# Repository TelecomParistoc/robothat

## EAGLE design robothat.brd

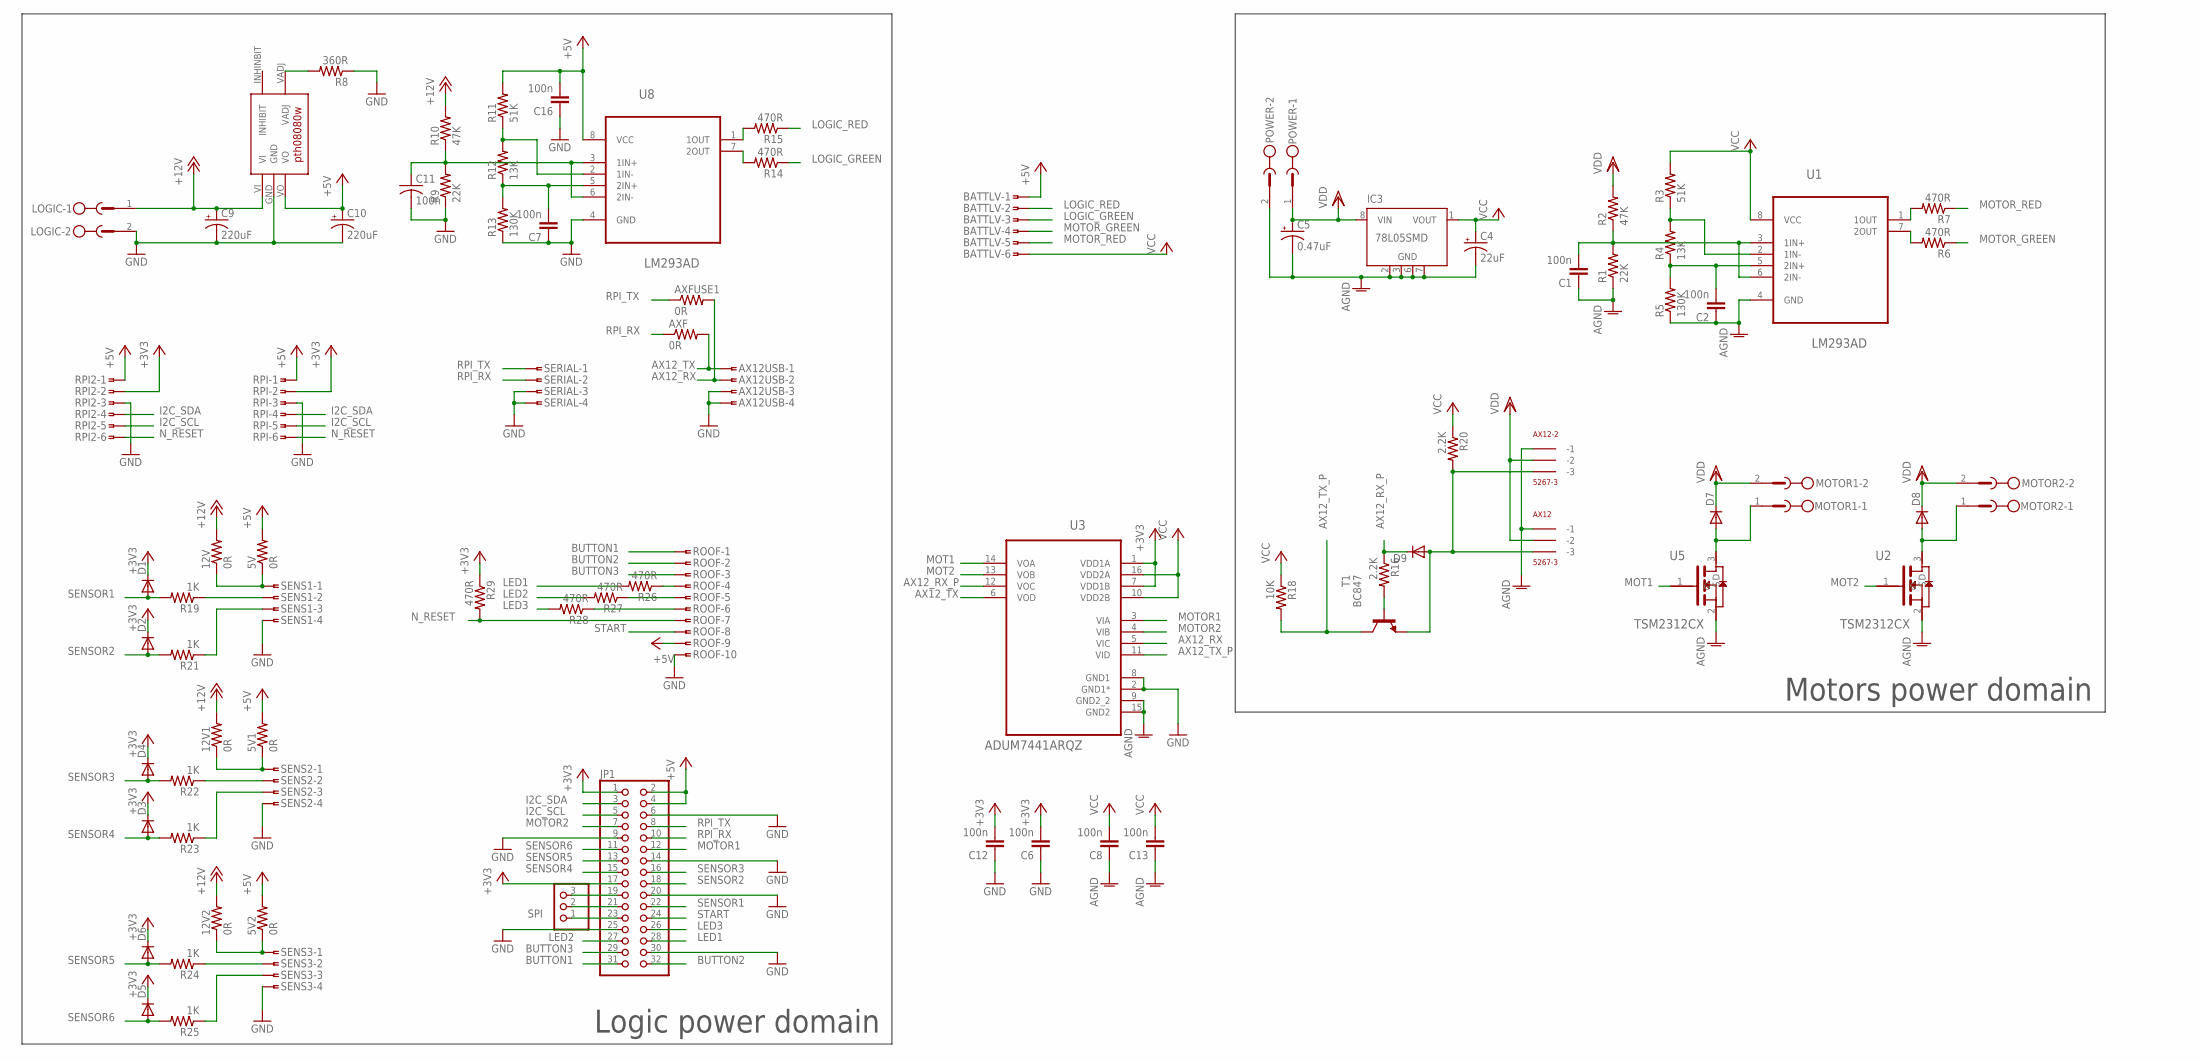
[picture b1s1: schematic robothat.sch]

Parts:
5V, 5V1, 5V2, 12V, 12V1, 12V2: 0R; R0805
AX12, AX12-2: 5267-3
AX12USB: SMDTOP-4; SMDTOP4
AXF: 0R; R0805
AXFUSE1: 0R; R0805
BATTLV: SMDTOP-6; SMDTOP6
C1, C2, C6, C7, C8, C11, C12, C13, C16: 100n; C0805
C4: 22uF; E2-5
C5: 0.47uF; E2-5
C9: 220uF; E3,5-8
C10: 220uF; E2,5-7
D1, D2, D3, D4, D5, D6, D9: DIODE-SOD523; SOD523
D7, D8: DIODE-SOD323-R; SOD323-R
IC3: 78L05SMD; SO08
JP1: PINHD-2X16; 2X16
LOGIC: MSTBV2
MOTOR1, MOTOR2: MSTBV2
POWER: MSTBV2
R1, R9: 22K; R0805
R2, R10: 47K; R0805
R3, R11: 51K; R0805
R4, R12: 13K; R0805
R5, R13: 130K; R0805
R6, R7, R14, R15, R26, R27, R28, R29: 470R; R0805
R8: 360R; R0805
R16, R20: 2.2K; R0805
R18: 10K; R0805
R19, R21, R22, R23, R24, R25: 1K; R0805
ROOF: SMDTOP-10; SMDTOP10
RPI, RPI2: SMDTOP-6; SMDTOP6
SENS1, SENS2, SENS3: SMDTOP-4; SMDTOP4
SERIAL: SMDTOP-4; SMDTOP4
SPI: PINHD-1X3; 1X03
T1: BC847; SOT23
U1, U8: LM293AD; SOIC127P600X175-8N
U2, U5: TSM2312CX; SOT95P280X130-3N
U3: ADUM7441ARQZ; SOP64P600X175-16N
U$2: REGUL_PTH

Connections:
+3V3: C6.2, C12.2, D1.C, D2.C, D3.C, D4.C, D5.C, D6.C, JP1.1, JP1.17, R29.1, RPI.2, RPI2.2, U3.1 (VDD1A), U3.7 (VDD1B)
+5V: 5V.2, 5V1.2, 5V2.2, BATTLV.1, C10.+, C16.2, JP1.2, JP1.4, R11.2, ROOF.9, RPI.1, RPI2.1, U8.8 (VCC), U$2.VO
+12V: 12V.2, 12V1.2, 12V2.2, C9.+, LOGIC.1, R10.2, U$2.VI
AGND: AX12.P$1 (-1), AX12-2.P$1 (-1), C1.1, C2.1, C4.-, C5.-, C8.1, C13.1, IC3.2 (GND), IC3.3 (GND), IC3.6 (GND), IC3.7 (GND), POWER.2, R1.1, R5.1, U1.4 (GND), U2.2 (S), U3.9 (GND2_2), U3.15 (GND2), U5.2 (S)
AX12_RX: AX12USB.2, AXFUSE1.2, U3.5 (VIC)
AX12_RX_P: D9.C, R16.1, U3.12 (VOC)
AX12_TX: AX12USB.1, AXF.2, U3.6 (VOD)
AX12_TX_P: R18.2, T1.3 (C), U3.11 (VID)
BUTTON1: JP1.31, ROOF.1
BUTTON2: JP1.32, ROOF.2
BUTTON3: JP1.29, ROOF.3
GND: AX12USB.3, AX12USB.4, C6.1, C7.1, C9.-, C10.-, C11.2, C12.1, C16.1, JP1.6, JP1.9, JP1.14, JP1.20, JP1.25, JP1.30, LOGIC.2, R8.1, R9.1, R13.1, ROOF.10, RPI.3, RPI2.3, SENS1.4, SENS2.4, SENS3.4, SERIAL.3, SERIAL.4, U3.2 (GND1*), U3.8 (GND1), U8.4 (GND), U$2.GND
I2C_SCL: JP1.5, RPI.5, RPI2.5
I2C_SDA: JP1.3, RPI.4, RPI2.4
LED1: JP1.28, R26.2
LED2: JP1.27, R27.2
LED3: JP1.26, R28.2
LOGIC_GREEN: BATTLV.3, R14.1
LOGIC_RED: BATTLV.2, R15.1
MOT1: U3.14 (VOA), U5.1 (G)
MOT2: U2.1 (G), U3.13 (VOB)
MOTOR1: JP1.12, U3.3 (VIA)
MOTOR2: JP1.7, U3.4 (VIB)
MOTOR_GREEN: BATTLV.4, R6.1
MOTOR_RED: BATTLV.5, R7.1
unnamed: R7.2, U1.1 (1OUT)
unnamed: D7.A, MOTOR1.1, U5.3 (D)
unnamed: R6.2, U1.7 (2OUT)
unnamed: D8.A, MOTOR2.1, U2.3 (D)
unnamed: C1.2, R1.2, R2.1, U1.3 (1IN+), U1.6 (2IN-)
unnamed: R3.1, R4.2, U1.2 (1IN-)
unnamed: C2.2, R4.1, R5.2, U1.5 (2IN+)
unnamed: 5V.1, 12V.1, SENS1.1
unnamed: 5V1.1, 12V1.1, SENS2.1
unnamed: R22.1, SENS2.2
unnamed: R19.1, SENS1.2
unnamed: R8.2, U$2.VADJ
unnamed: R15.2, U8.1 (1OUT)
unnamed: R14.2, U8.7 (2OUT)
unnamed: R21.1, SENS1.3
unnamed: C11.1, R9.2, R10.1, U8.3 (1IN+), U8.6 (2IN-)
unnamed: R11.1, R12.2, U8.2 (1IN-)
unnamed: C7.2, R12.1, R13.2, U8.5 (2IN+)
unnamed: R23.1, SENS2.3
unnamed: R16.2, T1.1 (B)
unnamed: AX12.P$3 (-3), AX12-2.P$3 (-3), D9.A, R20.2, T1.2 (E)
unnamed: 5V2.1, 12V2.1, SENS3.1
unnamed: R24.1, SENS3.2
unnamed: R25.1, SENS3.3
unnamed: R27.1, ROOF.5
unnamed: R26.1, ROOF.4
unnamed: R28.1, ROOF.6
unnamed: JP1.19, SPI.3
unnamed: JP1.21, SPI.2
unnamed: JP1.23, SPI.1
N_RESET: R29.2, ROOF.7, RPI.6, RPI2.6
RPI_RX: AXF.1, JP1.10, SERIAL.2
RPI_TX: AXFUSE1.1, JP1.8, SERIAL.1
SENSOR1: D1.A, JP1.22, R19.2
SENSOR2: D2.A, JP1.18, R21.2
SENSOR3: D4.A, JP1.16, R22.2
SENSOR4: D3.A, JP1.15, R23.2
SENSOR5: D6.A, JP1.13, R24.2
SENSOR6: D5.A, JP1.11, R25.2
START: JP1.24, ROOF.8
VCC: BATTLV.6, C4.+, C8.2, C13.2, IC3.1 (VOUT), R3.2, R18.1, R20.1, U1.8 (VCC), U3.10 (VDD2B), U3.16 (VDD2A)
VDD: AX12.P$2 (-2), AX12-2.P$2 (-2), C5.+, D7.C, D8.C, IC3.8 (VIN), MOTOR1.2, MOTOR2.2, POWER.1, R2.2

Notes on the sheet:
Logic power domain
Motors power domain

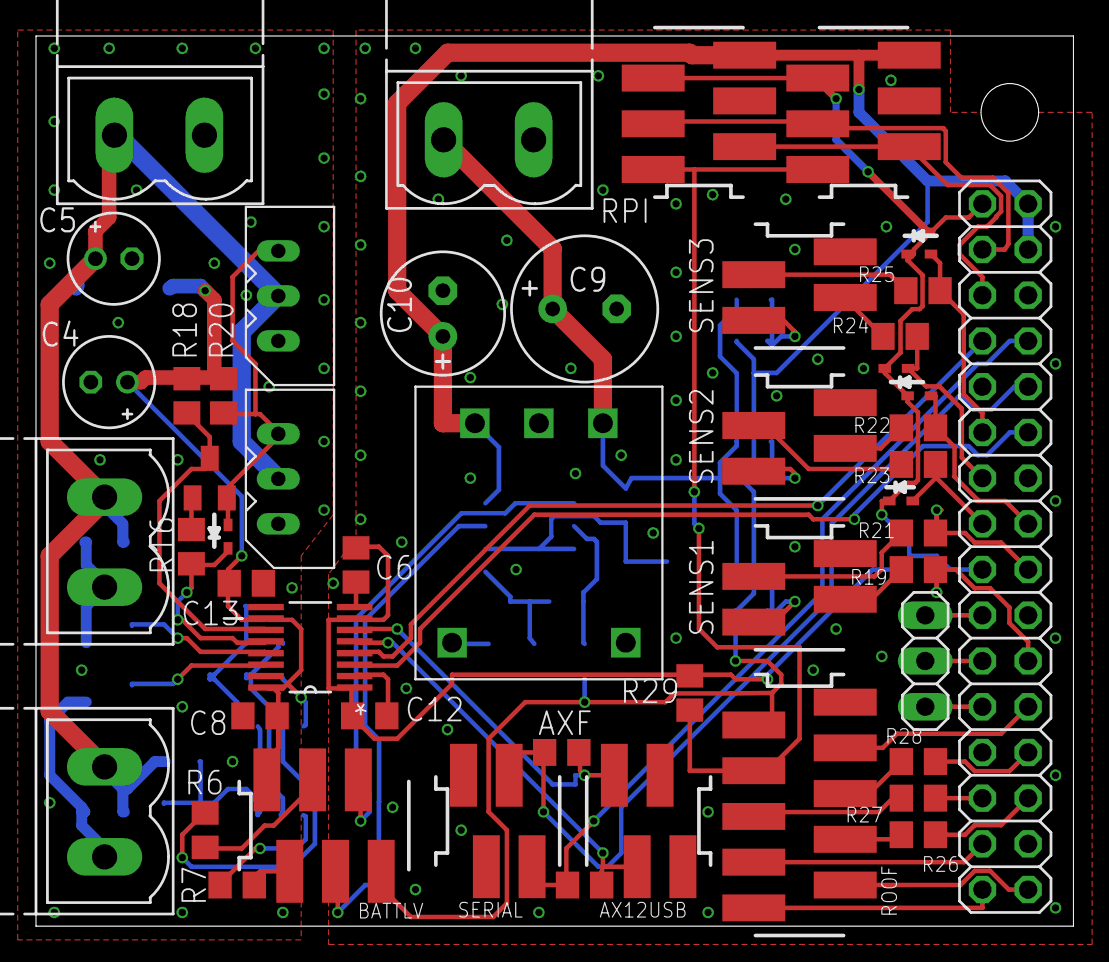
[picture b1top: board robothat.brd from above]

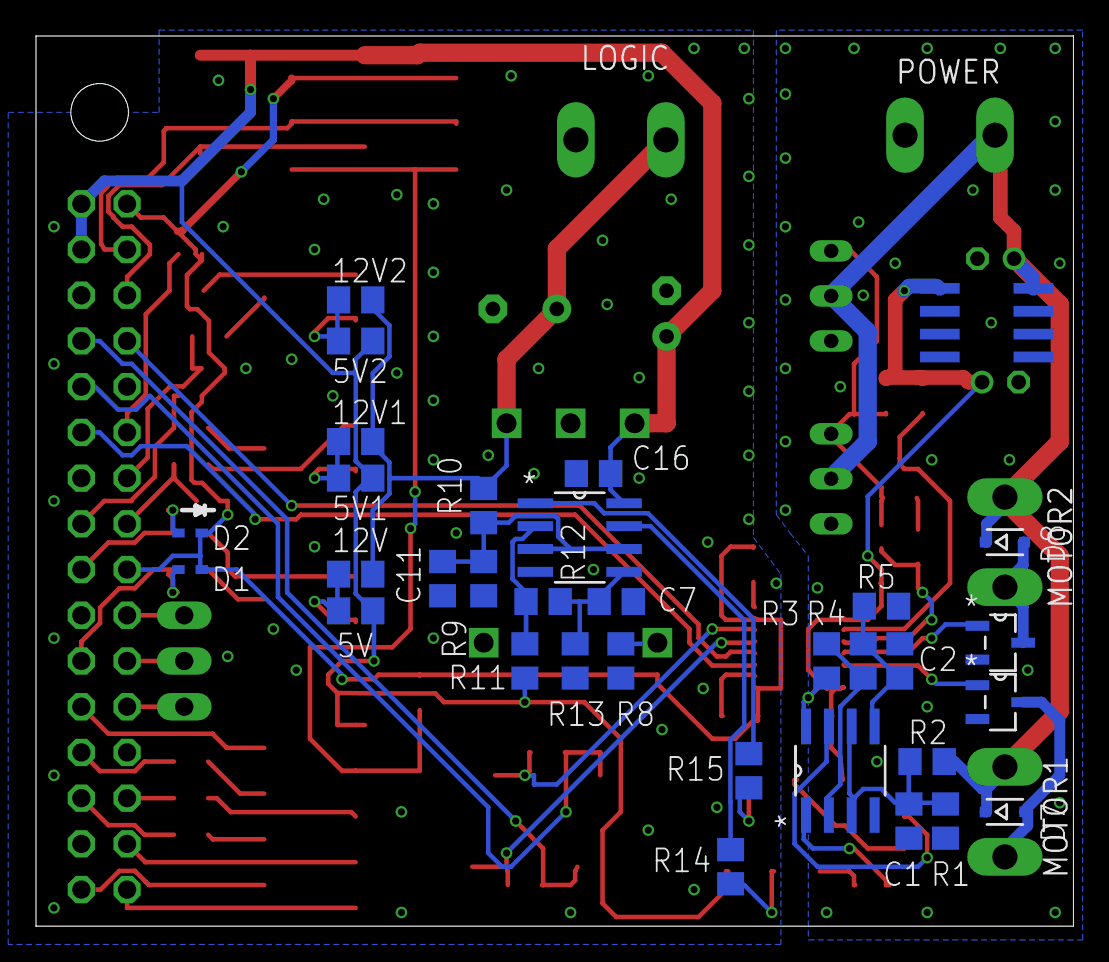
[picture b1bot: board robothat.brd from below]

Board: 2 copper layers, 57.6 x 49.5 mm, 83 parts (33 on the bottom side), 67 nets.

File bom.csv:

Qty,Qty to buy,Value,Device,Package,Parts,Description,Référence Farnell
2,,small signals,DIODE-SOD323-R,SOD323-R,D7  D8,DIODE,
7,,schottky,DIODE-SOD523,SOD523,D1  D2  D3  D4  D5  D6  D9,DIODE,
4,,,MSTBV2,MSTBV2,LOGIC  MOTOR1  MOTOR2  POWER,PHOENIX,
1,0,,PINHD-1X3,1X03,SPI,PIN HEADER,/
1,1,,PINHD-2X16,2X16,JP1,PIN HEADER,1668393
1,,,SMDTOP-10,SMDTOP10,ROOF,AMP connector,
5,,,SMDTOP-4,SMDTOP4,AX12USB  SENS1  SENS2  SENS3  SERIAL,AMP connector,
3,,,SMDTOP-6,SMDTOP6,BATTLV  RPI  RPI2,AMP connector,
1,0,0.47uF,CPOL-USE2-5,E2-5,C5,POLARIZED CAPACITOR,/
8,0,0R,R-US_R0805,R0805,5V  5V1  5V2  12V  12V1  12V2  AXF  AXFUSE1,RESISTOR,/
9,0,100n,C-EUC0805,C0805,C1  C2  C6  C7  C8 C11 C12  C13  C16,CAPACITOR,/
1,0,10K,R-US_R0805,R0805,R18,RESISTOR,/
2,0,130K,R-US_R0805,R0805,R5  R13,RESISTOR,/
2,0,13K,R-US_R0805,R0805,R4  R12,RESISTOR,/
6,0,1K,R-US_R0805,R0805,R19  R21  R22  R23  R24  R25,RESISTOR,/
2,0,2.2K,R-US_R0805,R0805,R16  R20,RESISTOR,/
1,0,220uF,CPOL-USE2.5-7,E2 5-7,C10,POLARIZED CAPACITOR,/
1,0,220uF,CPOL-USE3.5-8,E3 5-8,C9,POLARIZED CAPACITOR,/
2,0,22K,R-US_R0805,R0805,R1  R9,RESISTOR,/
1,0,22uF,CPOL-USE2-5,E2-5,C4,POLARIZED CAPACITOR,/
1,0,360R,R-US_R0805,R0805,R8,RESISTOR,/
8,0,470R,R-US_R0805,R0805,R6  R7  R14  R15  R26  R27  R28  R29,RESISTOR,/
2,0,47K,R-US_R0805,R0805,R2  R10,RESISTOR,/
2,0,51K,R-US_R0805,R0805,R3  R11,RESISTOR,/
2,,5267-3,5267-3,5267-3,AX12  AX12-2,,9979620
1,,78L05SMD,78L05SMD,SO08,IC3,VOLTAGE REGULATOR,
1,0,ADUM7441ARQZ,ADUM7441ARQZ,SOP64P600X175-16N,U3,Quad-Channel Digital Isolators,/
1,0,BC847,BC847,SOT23,T1,NPN TRANSISTOR,/
2,2,LM293AD,LM293AD,SOIC127P600X175-8N,U1  U8,DUAL COMPARATORS,2382616
1,0,REGUL_PTH,REGUL_PTH,REGUL_PTH,U$2,pth08080w,/
2,0,TSM2312CX,TSM2306CX,SOT95P280X130-3N,U2  U5,N-Channel MOSFET,/

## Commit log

2017-04-26 schematic and beginning of place
2017-04-26 finished first place
2017-05-02 routing and silkscreen done
2017-05-15 added schematic and pcb in pdf, added BOM
2017-05-16 added farnell refs
2018-05-08 mapping update for 2018
